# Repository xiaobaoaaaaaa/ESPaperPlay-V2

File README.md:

# ESPaperPlay-V2

基于 **ESP32-S3-WROOM-1-N16R8 + 7.5 英寸电子纸**的多功能平台，逐步实现阅读、音频和网络应用。

这是从 [ESPaperPlay](https://github.com/xiaobaoaaaaaa/ESPaperPlay) 拆分的独立重构仓库。旧版代码的参考起点为 [`0f6d7c3`](https://github.com/xiaobaoaaaaaa/ESPaperPlay/tree/0f6d7c349afdbbeb962a736d84036ce7f8487174)。本库从当前 V2 基线建立新的提交历史，不包含旧固件工程。

## 当前状态

- **当前硬件开发：99 × 99 mm 嘉立创EDA原生工程。** 已完成原生 PCB 布线、标准四层叠层保存和完整 21 项复核，原生 DRC 为 0 连接/0 其他错误，工程审查项仍保留；实际 CAM 及工程审查结论见[原生工程入口](hardware/devboard-99/easyeda-native/README.md)和[同版检查点](hardware/devboard-99/easyeda-native/audit/checkpoint-status.json)。[KiCad r14](hardware/devboard-99/README.md)保留为先期完整布线与电路参考，其独立复核及制造/装配边界见[r14记录](hardware/devboard-99/review-r14/README.md)。尚未制造或实板验证，当前检查不代表制造放行。
- 首批计划做 5 块 PCB，先装 2 块。当前装配资料含元件方向图、手焊接口清单及专用顶层钢网。[99 mm 首板装配资料](hardware/devboard-99/easyeda-native/audit/assembly-review/README.md)
- **固件：M0 骨架。** 应用宿主、活动租约、休眠准备契约、板级配置检查、双槽分区和串口演示已经实现；外设驱动、图形界面和网络应用尚待接入。
- **保留基线：r10 PCB 制造整改完成。** 已移动64个近焊盘过孔，538个普通孔的双面阻焊间距达到≥0.20mm，11个IC热孔指定填平盖帽；官方USB/SD名义阻抗窗口检查通过。原理图r6/r5保持，DRC为0错误、0未连接；已更新独立制板、DIY钢网及203位回流/27位手焊文件，尚未下单或上电。见 [r10记录](docs/v2/hardware/pcb-dfm-r10.md)和[文件包](hardware/devboard-r0/output/manufacturing/r10-review/README.md)。这些制造文件不适用于当前 99 mm 板。
- **历史 r10 首批准备（r11 记录）：** 已按5块PCB、先焊2块及无框钢片整理[工厂审核规格、64种备料表与首板工作单](hardware/devboard-r0/output/manufacturing/r10-first-batch/README.md)。该清单对应旧 r10 PCB，不适用于当前 99 mm 原生工程；当时工厂回复、来料容量和实测未完成。现有 M0 不具备分域维护功能。
- **历史 r10 嘉立创迁移与 CAM：** [旧迁移工程与独立制板/钢网包](hardware/devboard-r0/output/easyeda/r10-cam-checked/README.md)已纳入Git；[最终CAM复核](hardware/devboard-r0/output/easyeda/r10-cam-checked/CAM_REVIEW.md)通过、严格DRC为0。已恢复导入遗漏的阻焊、热焊及铜颈设置；原 KiCad r10 和原制造包仅保留历史对照；该包不能用于当前 99 mm 原生板。
- 未进行新板烧录或上电验证。硬件的充电默认禁用状态、温窗假设及待验证项见硬件文档。

## 目录与入口

| 目录 | 内容 |
| --- | --- |
| [根目录固件工程](docs/v2/firmware.md) | 独立 ESP-IDF 固件、主机测试及板级元数据 |
| [docs/v2/](docs/v2/README.md) | 架构、路线和软硬件设计记录 |
| [hardware/devboard-r0/](hardware/devboard-r0/README.md) | 历史 KiCad r10 基线、嘉立创迁移工程、项目库、检查器和评审记录 |
| [hardware/devboard-99/](hardware/devboard-99/README.md) | 99 mm 开发板：当前嘉立创EDA原生工程及 KiCad r14 对照、原生检查/装配条件 |
| [hardware/reference/](hardware/reference/) | 原厂来源、版本与 SHA-256；原始下载文件仅本地保存 |
| [outputs/](outputs/) | 已审查的 BOM 工作簿 |

设计资料保留 `docs/v2/` 和 `devboard-r0` 路径，使原有工程、检查器及证据链接继续有效；这些目录名不表示当前硬件仍是 r0。

## 验证

主机测试不需要 ESP-IDF：

```sh
cmake -S tests -B build/host -G Ninja \
  -DCMAKE_C_COMPILER=clang -DCMAKE_BUILD_TYPE=Debug
cmake --build build/host
ctest --test-dir build/host --output-on-failure
```

激活 ESP-IDF 6.1 后构建 N16R8 固件：

```sh
idf.py -B build/esp32s3 build
```

固件详细说明见 [固件开发指南](docs/v2/firmware.md)。当前硬件检查命令见 [原生工程说明](hardware/devboard-99/easyeda-native/README.md)和[完整验证入口](hardware/devboard-99/easyeda-native/verification/README-final-runner.md)；公开文件完整性可运行 `python3 tools/verify_repository.py`。原厂 PDF 不随 Git 分发，重新计算依赖 PDF 的温窗模型前，须按相应 `sources.json` 恢复资料。

## 版本管理

`main` 保存已提交的阶段成果，功能开发使用短期分支。硬件设计修订号与 Git 标签分别管理，r5/r6/r7 的历史报告不是对应的历史提交。迁移来源、检查结果和当前基线见 [迁移记录](docs/v2/repository-migration.md)。

当前嘉立创工程入口见[99 mm 原生工程](hardware/devboard-99/easyeda-native/README.md)；旧 r10 迁移历史快照见[历史迁移目录](hardware/devboard-r0/output/easyeda/README.txt)，KiCad r10 仅保留为迁移对照基线。两种工程不会自动双向同步；每次变更须注明所编辑的工程及来源版本，同步更新导出、检查报告与校验清单。历史生成脚本不能覆盖已经手工修改的原理图或PCB。

本项目原创代码与文档沿用 [MIT License](LICENSE)。KiCad 库内容及原厂资料的归属见 [第三方说明](THIRD_PARTY_NOTICES.md)。

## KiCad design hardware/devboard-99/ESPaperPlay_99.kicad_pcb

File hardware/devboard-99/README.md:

# ESPaperPlay 99 mm 开发验证板

当前设计入口为[嘉立创EDA原生工程](easyeda-native/README.md)，以下保留 KiCad r14 的独立参考与复核结果。

**r14：99 × 99 mm、四层、顶面装配；已完成PCB布线与CAD复核。原生DRC 0违规、0未连接、0原理图一致性问题。**

用 KiCad 10 打开本目录的 [ESPaperPlay_99.kicad_pro](ESPaperPlay_99.kicad_pro)，再打开同名PCB，即本次完整走线版。包含独立根原理图、10张子页、本地符号/封装库和规则文件。

保留240个封装、236个电气器件、774个逻辑引脚和181个网络。全部器件仍在顶面，五个按键及全部调试/测流接口、21个操作包络保留。原理图、器件位置、焊盘几何、引脚分配与DNP状态保持r13；原r10和嘉立创迁移工程未修改。

| 项目 | 当前状态 |
|---|---|
| 外形与层叠 | Edge.Cuts中心线99.000×99.000mm；四层名义1.6mm；F/B走线，双内层连续GND |
| 实际布线 | 2591段走线、665个普通过孔；最小线宽/间距0.15mm，普通孔至少0.30/0.60mm |
| 电源与接口 | 24条电源铜路径预算通过；6路SD主路径长度/偏差检查通过；USB两方向差分长度差已量化 |
| 孔与阻焊 | 全部实际孔距与普通过孔双面阻焊距离通过名义几何检查；制造公差仍待厂方验收 |
| 热孔 | U101四个实际普通开窗PTH及圆弧钢网保持；U301十二孔保持；U201/U203/U802八个外移GND孔已实际接通 |
| 充电 | 仍默认禁充：R108 DNP、J105开放；设定电流约0.701A，电池/NTC适配与实测条件保持 |

完整结果、USB回流目标例外、参考面边缘条件及U101印刷/制造验收边界见 [r14复核记录](review-r14/README.md)。[顶面走线](review-r14/front-layout.png)、[装配图](review-r14/assembly-layout.png)、[操作空间](review-r14/access-layout.png)均对应当前PCB。

裸板尺寸满足10×10cm内的目标，表面处理参考OSP；没有要求U101树脂填孔或电镀盖帽，也没有请求或证明±10%阻抗保证。实际叠层、孔环/阻焊和钢网精度、首板焊接/温升/信号完整性仍待验收；CAD通过不代表免费券资格或制造放行。U101局部手工印刷须核验每轴≤±0.030mm对位、钢网边缘≤±0.020mm条件，详见 [r13公差记录](review-r13/README.md)。

已按确认流程在嘉立创EDA使用既有库建立独立原生工程，原生标准四层叠层已保存重开。当前布线、原生 DRC、实际 CAM、工程偏差和首板条件统一见[原生工程检查点](easyeda-native/README.md)；本页前述 r14 数字是 KiCad 对照结果，不等同于原生工程检查结论。尚未制造放行，未上传工厂或下单；旧 r10 制板和钢网包不能用于本 99 mm 版。

历史依据：[r12布局/机械基线](review-r12/layout-review.md)、[r13热孔与钢网](review-r13/README.md)。复现检查见 [工具说明](tools/README.md)。

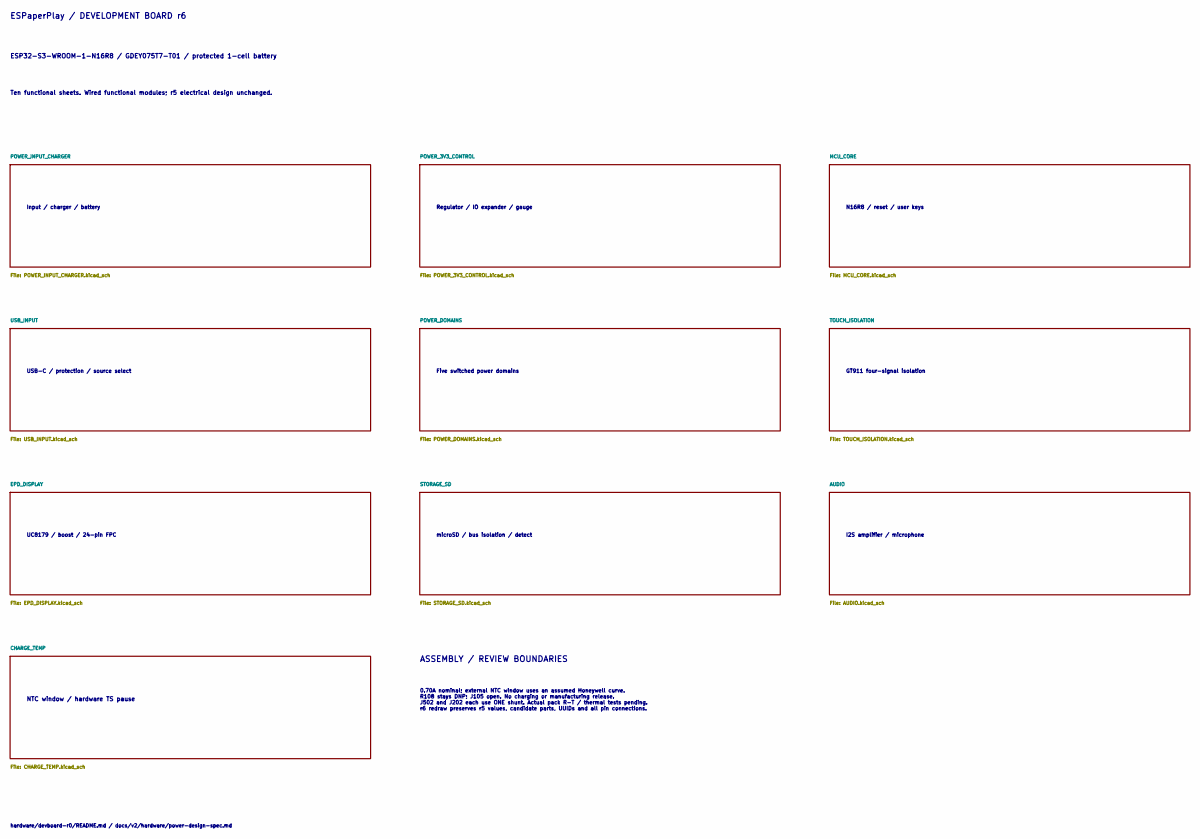
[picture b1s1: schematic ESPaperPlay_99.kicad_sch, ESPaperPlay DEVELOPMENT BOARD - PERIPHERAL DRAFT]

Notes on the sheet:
ESPaperPlay / DEVELOPMENT BOARD r6
ESP32-S3-WROOM-1-N16R8 / GDEY075T7-T01 / protected 1-cell battery
Ten functional sheets. Wired functional modules; r5 electrical design unchanged.
Input / charger / battery
Regulator / IO expander / gauge
N16R8 / reset / user keys
USB-C / protection / source select
Five switched power domains
GT911 four-signal isolation
UC8179 / boost / 24-pin FPC
microSD / bus isolation / detect
I2S amplifier / microphone
ASSEMBLY / REVIEW BOUNDARIES
0.70A nominal; external NTC window uses an assumed Honeywell curve. R108 stays DNP; J105 open. No charging or manufacturing release. J502 and J202 each use ONE shunt. Actual pack R-T / thermal tests pending. r6 redraw preserves r5 values, candidate parts, UUIDs and all pin connections.
hardware/devboard-r0/README.md / docs/v2/hardware/power-design-spec.md
NTC window / hardware TS pause

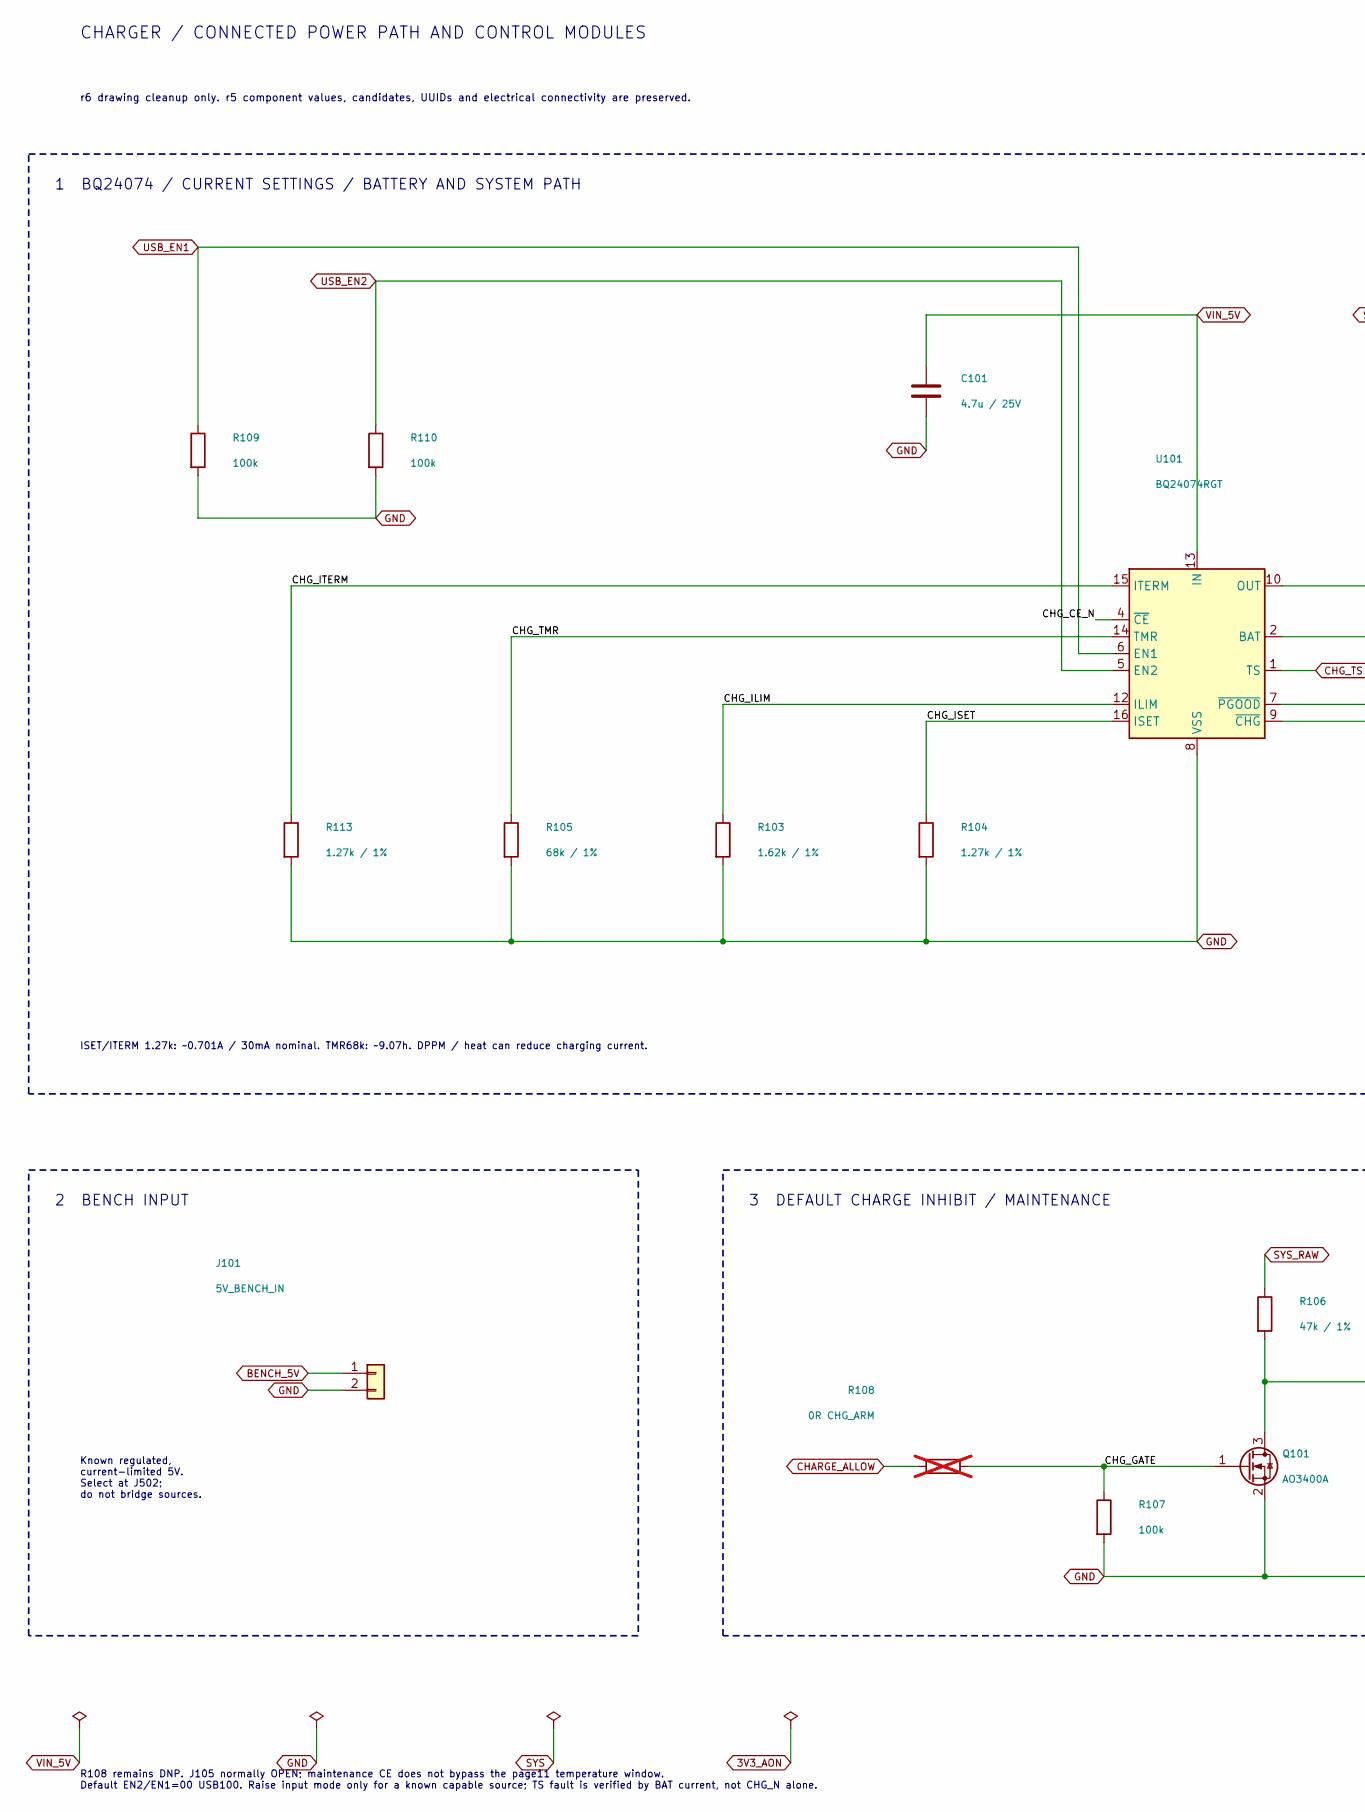
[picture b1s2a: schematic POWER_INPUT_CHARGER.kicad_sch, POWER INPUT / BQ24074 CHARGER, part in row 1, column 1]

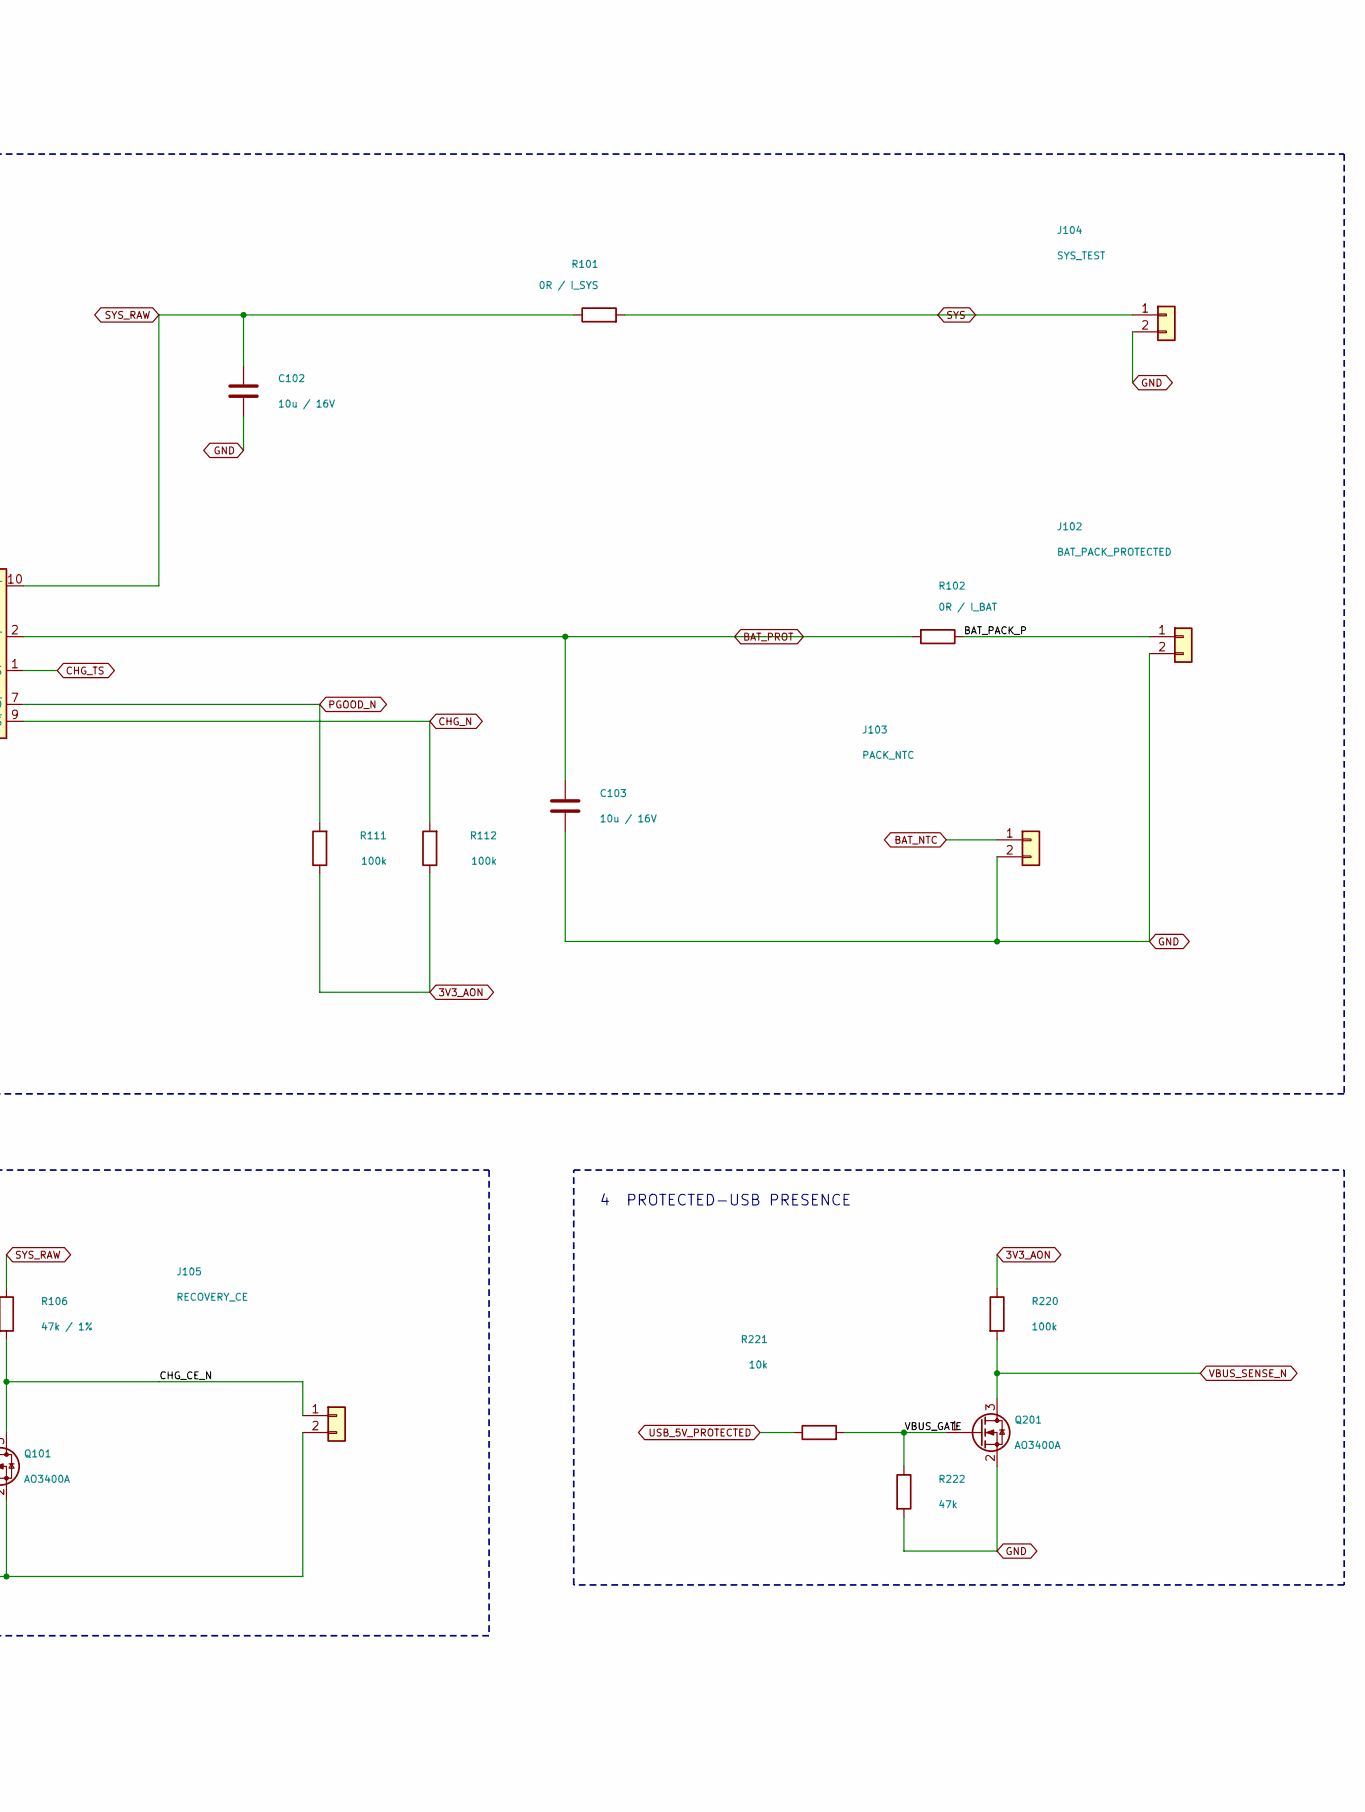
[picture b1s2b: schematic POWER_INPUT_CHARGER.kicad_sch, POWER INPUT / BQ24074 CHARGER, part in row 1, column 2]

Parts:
C101: 4.7u / 25V; C_0805_2012Metric
C102, C103: 10u / 16V; C_1206_3216Metric
J101: 5V_BENCH_IN; WR_PHD_1x02_P2.54_Drill1.10
J102: BAT_PACK_PROTECTED; PhoenixContact_MKDS-1-2-3.5_1751248_1x02_P3.50mm_Horizontal
J103: PACK_NTC; PhoenixContact_MKDS-1-2-3.5_1751248_1x02_P3.50mm_Horizontal
J104: SYS_TEST; WR_PHD_1x02_P2.54_Drill1.10
J105: RECOVERY_CE; WR_PHD_1x02_P2.54_Drill1.10
Q101, Q201: AO3400A; AOS_SOT23_PO00001N
R101: 0R / I_SYS; Bourns_CRF0805_Jumper
R102: 0R / I_BAT; Bourns_CRF0805_Jumper
R103: 1.62k / 1%; R_0603_1608Metric
R104, R113: 1.27k / 1%; R_0603_1608Metric
R105: 68k / 1%; R_0603_1608Metric
R106: 47k / 1%; R_0603_1608Metric
R107, R109, R110, R111, R112, R220: 100k; R_0603_1608Metric
R108: 0R CHG_ARM; R_0603_1608Metric; not fitted
R221: 10k; R_0603_1608Metric
R222: 47k; R_0603_1608Metric
U101: BQ24074RGT; TI_RGT0016C_VQFN_3x3mm_P0.5mm_EP1.68mm

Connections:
3V3_AON: R111.1, R112.1, R220.1; also elsewhere on the board
/POWER_INPUT_CHARGER/BAT_PACK_P: J102.1, R102.1
/POWER_INPUT_CHARGER/CHG_CE_N: J105.1, Q101.3 (D), R106.2, U101.4 (~CE)
/POWER_INPUT_CHARGER/CHG_GATE: Q101.1 (G), R107.1, R108.2
/POWER_INPUT_CHARGER/CHG_ILIM: R103.1, U101.12 (ILIM)
/POWER_INPUT_CHARGER/CHG_ISET: R104.1, U101.16 (ISET)
/POWER_INPUT_CHARGER/CHG_ITERM: R113.1, U101.15 (ITERM)
/POWER_INPUT_CHARGER/CHG_TMR: R105.1, U101.14 (TMR)
/POWER_INPUT_CHARGER/VBUS_GATE: Q201.1 (G), R221.2, R222.1
BAT_NTC: J103.1; also elsewhere on the board
BAT_PROT: C103.1, R102.2, U101.2 (BAT), U101.3 (BAT); also elsewhere on the board
BENCH_5V: J101.1; also elsewhere on the board
CHARGE_ALLOW: R108.1; also elsewhere on the board
CHG_N: R112.2, U101.9 (~CHG); also elsewhere on the board
CHG_TS: U101.1 (TS); also elsewhere on the board
GND: C101.2, C102.2, C103.2, J101.2, J102.2, J103.2, J104.2, J105.2, Q101.2 (S), Q201.2 (S), R103.2, R104.2, R105.2, R107.2, R109.2, R110.2, R113.2, R222.2, U101.8 (VSS), U101.17 (VSS); also elsewhere on the board
PGOOD_N: R111.2, U101.7 (~PGOOD); also elsewhere on the board
SYS: J104.1, R101.2; also elsewhere on the board
SYS_RAW: C102.1, R101.1, R106.1, U101.10 (OUT), U101.11 (OUT)
USB_5V_PROTECTED: R221.1; also elsewhere on the board
USB_EN1: R109.1, U101.6 (EN1); also elsewhere on the board
USB_EN2: R110.1, U101.5 (EN2); also elsewhere on the board
VBUS_SENSE_N: Q201.3 (D), R220.2; also elsewhere on the board
VIN_5V: C101.1, U101.13 (IN); also elsewhere on the board

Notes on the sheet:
CHARGER / CONNECTED POWER PATH AND CONTROL MODULES
r6 drawing cleanup only. r5 component values, candidates, UUIDs and electrical connectivity are preserved.
1 BQ24074 / CURRENT SETTINGS / BATTERY AND SYSTEM PATH
ISET/ITERM 1.27k: ~0.701A / 30mA nominal. TMR68k: ~9.07h. DPPM / heat can reduce charging current.
2 BENCH INPUT
Known regulated, current-limited 5V. Select at J502; do not bridge sources.
3 DEFAULT CHARGE INHIBIT / MAINTENANCE
4 PROTECTED-USB PRESENCE
R108 remains DNP. J105 normally OPEN; maintenance CE does not bypass the page11 temperature window. Default EN2/EN1=00 USB100. Raise input mode only for a known capable source; TS fault is verified by BAT current, not CHG_N alone.

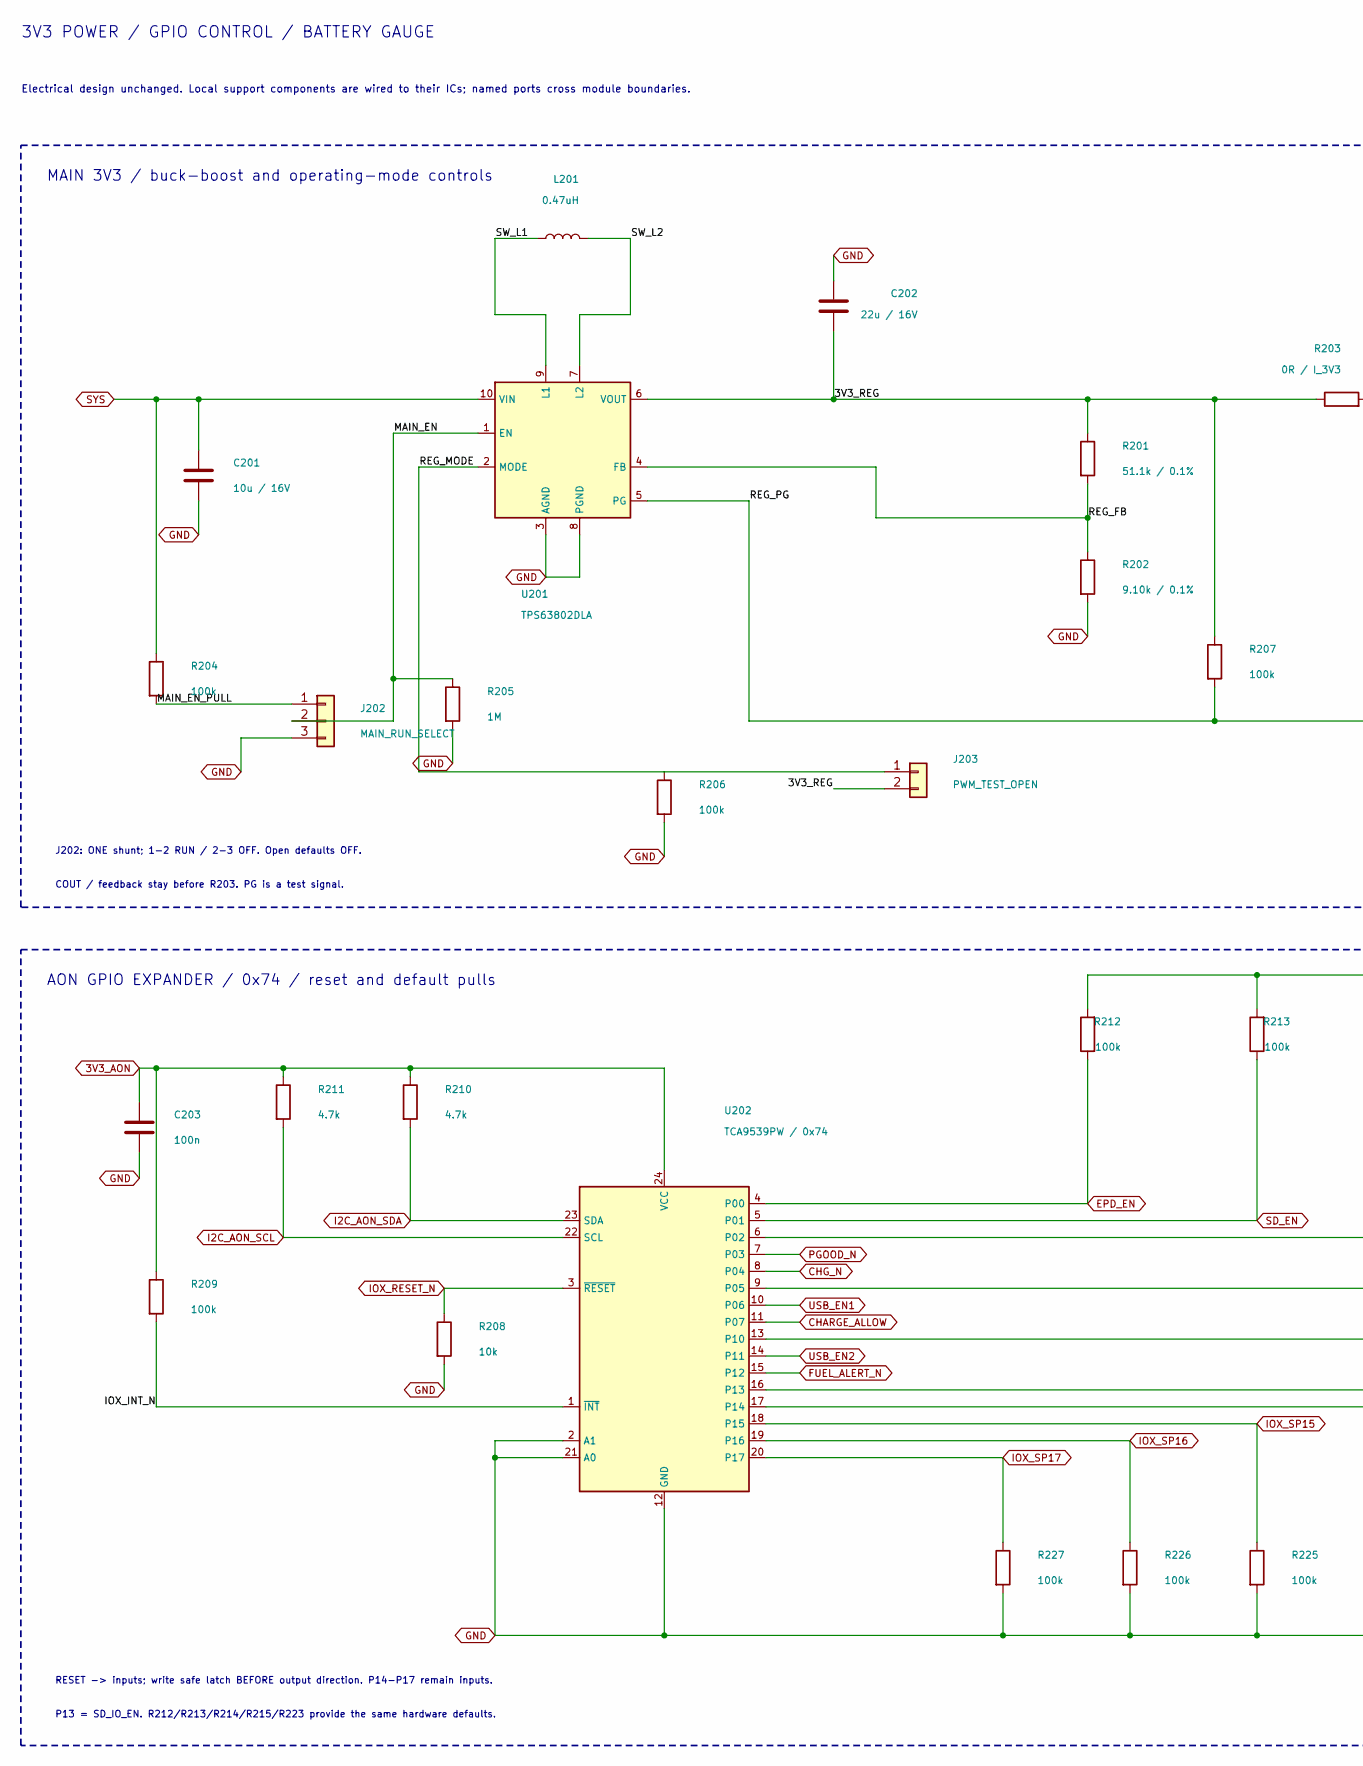
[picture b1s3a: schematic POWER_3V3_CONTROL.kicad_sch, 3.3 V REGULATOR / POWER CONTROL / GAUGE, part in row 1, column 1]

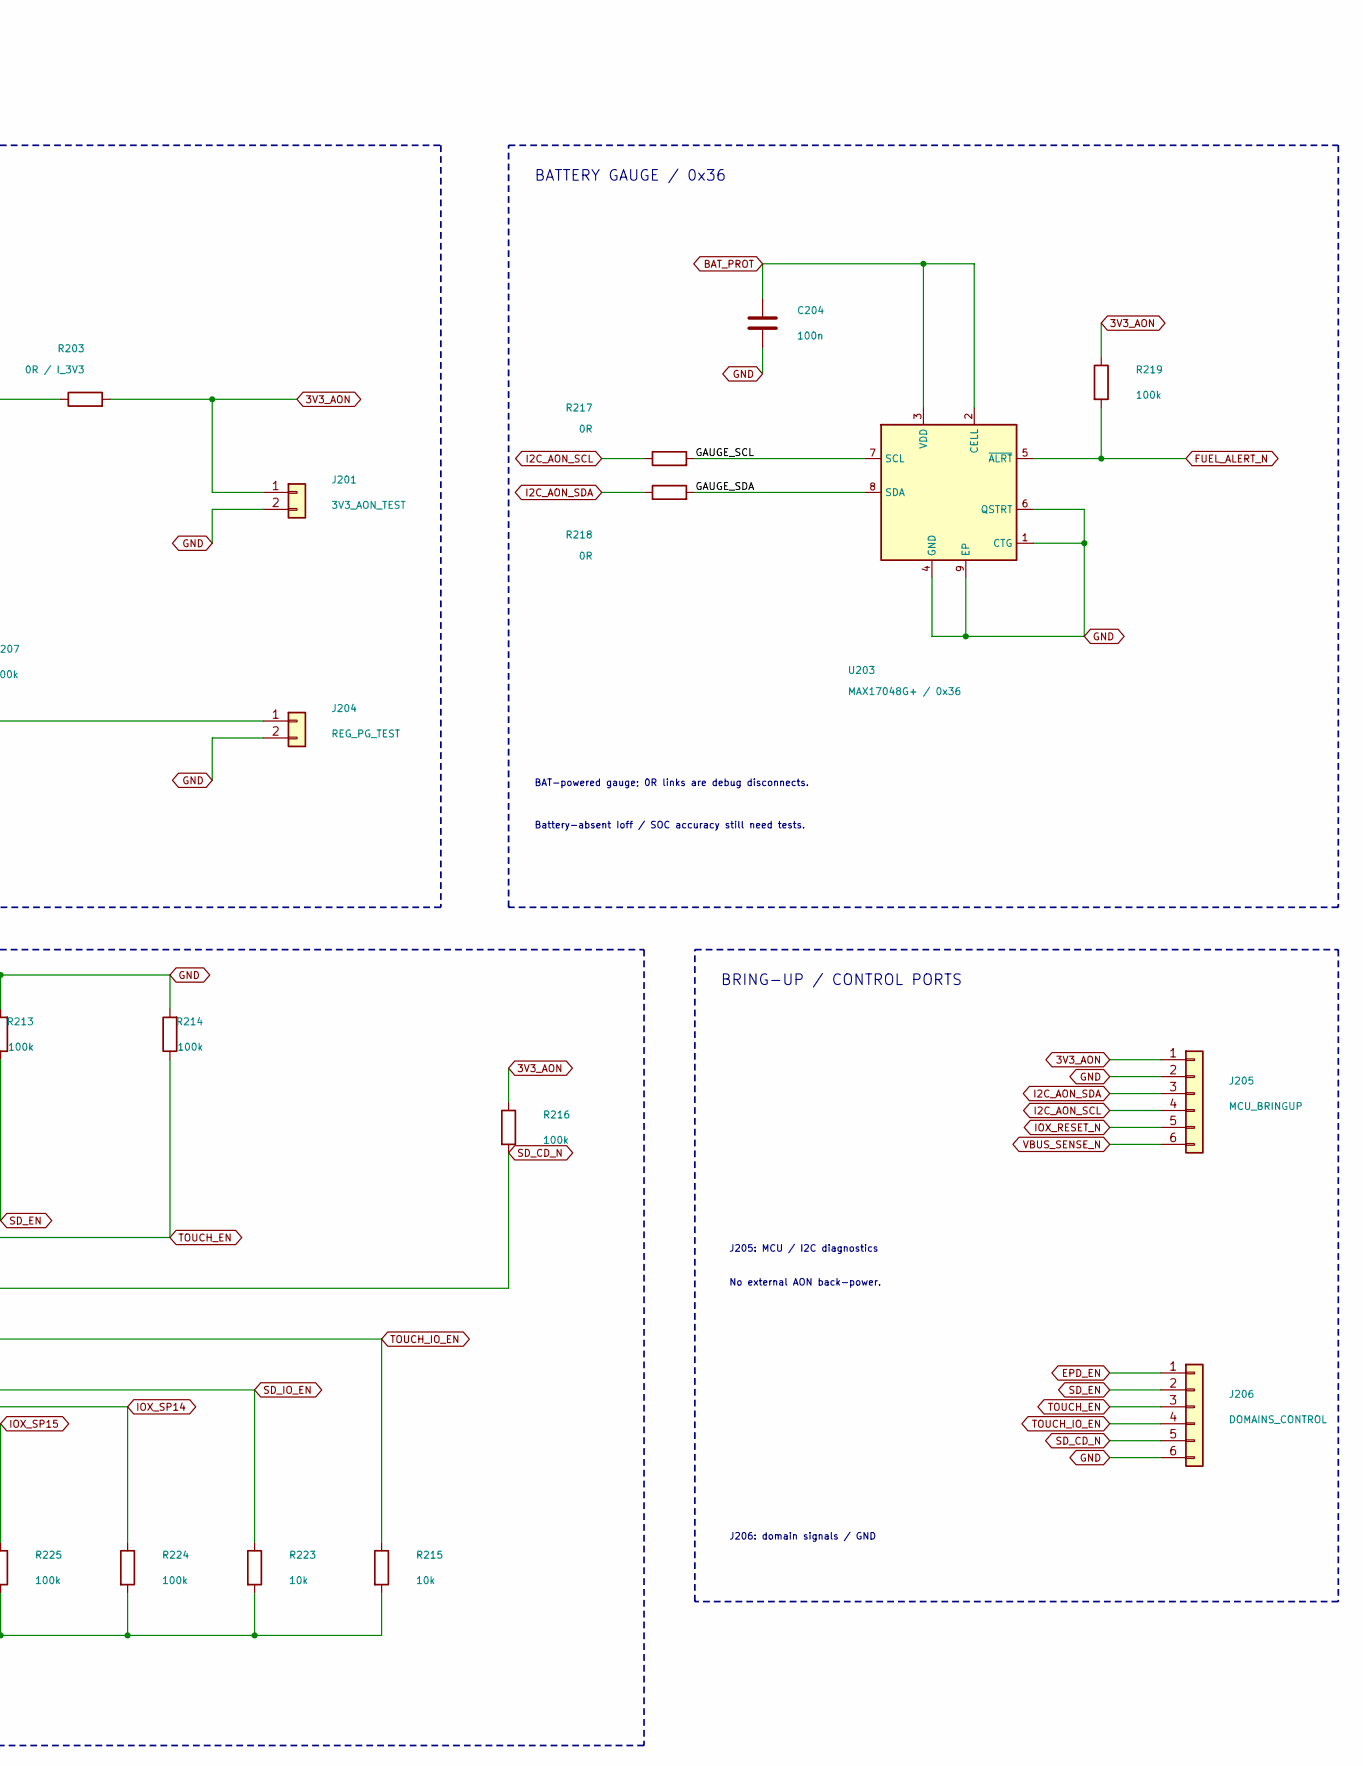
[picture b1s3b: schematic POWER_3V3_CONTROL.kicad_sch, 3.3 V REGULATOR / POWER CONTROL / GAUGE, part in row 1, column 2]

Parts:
C201: 10u / 16V; C_1206_3216Metric
C202: 22u / 16V; C_1206_3216Metric
C203, C204: 100n; C_0603_1608Metric
J201: 3V3_AON_TEST; WR_PHD_1x02_P2.54_Drill1.10
J202: MAIN_RUN_SELECT; WR_PHD_1x03_P2.54_Drill1.10
J203: PWM_TEST_OPEN; WR_PHD_1x02_P2.54_Drill1.10
J204: REG_PG_TEST; WR_PHD_1x02_P2.54_Drill1.10
J205: MCU_BRINGUP; WR_PHD_1x06_P2.54_Drill1.10
J206: DOMAINS_CONTROL; WR_PHD_1x06_P2.54_Drill1.10
L201: 0.47uH; Coilcraft_XFL4015_4x4mm
R201: 51.1k / 0.1%; R_0603_1608Metric
R202: 9.10k / 0.1%; R_0603_1608Metric
R203: 0R / I_3V3; Bourns_CRF0805_Jumper
R204, R206, R207, R209, R212, R213, R214, R216, R219, R224, R225, R226, R227: 100k; R_0603_1608Metric
R205: 1M; R_0603_1608Metric
R208, R215, R223: 10k; R_0603_1608Metric
R210, R211: 4.7k; R_0603_1608Metric
R217, R218: 0R; R_0603_1608Metric
U201: TPS63802DLA; TI_DLA0010A_VSON-HR_2x3mm_P0.5mm
U202: TCA9539PW / 0x74; TSSOP-24_4.4x7.8mm_P0.65mm
U203: MAX17048G+ / 0x36; TDFN-8-1EP_2x2mm_P0.5mm_EP0.8x1.2mm

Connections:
3V3_AON: C203.1, J201.1, J205.1, R203.2, R209.1, R210.1, R211.1, R216.1, R219.1, U202.24 (VCC); also elsewhere on the board
/POWER_3V3_CONTROL/3V3_REG: C202.1, J203.2, R201.1, R203.1, R207.1, U201.6 (VOUT)
/POWER_3V3_CONTROL/GAUGE_SCL: R217.2, U203.7 (SCL)
/POWER_3V3_CONTROL/GAUGE_SDA: R218.2, U203.8 (SDA)
/POWER_3V3_CONTROL/IOX_INT_N: R209.2, U202.1 (~INT)
/POWER_3V3_CONTROL/MAIN_EN: J202.2, R205.1, U201.1 (EN)
/POWER_3V3_CONTROL/MAIN_EN_PULL: J202.1, R204.2
/POWER_3V3_CONTROL/REG_FB: R201.2, R202.1, U201.4 (FB)
/POWER_3V3_CONTROL/REG_MODE: J203.1, R206.1, U201.2 (MODE)
/POWER_3V3_CONTROL/REG_PG: J204.1, R207.2, U201.5 (PG)
/POWER_3V3_CONTROL/SW_L1: L201.1, U201.9 (L1)
/POWER_3V3_CONTROL/SW_L2: L201.2, U201.7 (L2)
BAT_PROT: C204.1, U203.2 (CELL), U203.3 (VDD); also elsewhere on the board
CHARGE_ALLOW: U202.11 (P07); also elsewhere on the board
CHG_N: U202.8 (P04); also elsewhere on the board
EPD_EN: J206.1, R212.1, U202.4 (P00); also elsewhere on the board
FUEL_ALERT_N: R219.2, U202.15 (P12), U203.5 (~ALRT)
GND: C201.2, C202.2, C203.2, C204.2, J201.2, J202.3, J204.2, J205.2, J206.6, R202.2, R205.2, R206.2, R208.2, R212.2, R213.2, R214.2, R215.2, R223.2, R224.2, R225.2, R226.2, R227.2, U201.3 (AGND), U201.8 (PGND), U202.2 (A1), U202.12 (GND), U202.21 (A0), U203.1 (CTG), U203.4 (GND), U203.6 (QSTRT), U203.9 (EP); also elsewhere on the board
I2C_AON_SCL: J205.4, R211.2, R217.1, U202.22 (SCL); also elsewhere on the board
I2C_AON_SDA: J205.3, R210.2, R218.1, U202.23 (SDA); also elsewhere on the board
IOX_RESET_N: J205.5, R208.1, U202.3 (~RESET); also elsewhere on the board
IOX_SP14: R224.1, U202.17 (P14)
IOX_SP15: R225.1, U202.18 (P15)
IOX_SP16: R226.1, U202.19 (P16)
IOX_SP17: R227.1, U202.20 (P17)
PGOOD_N: U202.7 (P03); also elsewhere on the board
SD_CD_N: J206.5, R216.2, U202.9 (P05); also elsewhere on the board
SD_EN: J206.2, R213.1, U202.5 (P01); also elsewhere on the board
SD_IO_EN: R223.1, U202.16 (P13); also elsewhere on the board
SYS: C201.1, R204.1, U201.10 (VIN); also elsewhere on the board
TOUCH_EN: J206.3, R214.1, U202.6 (P02); also elsewhere on the board
TOUCH_IO_EN: J206.4, R215.1, U202.13 (P10); also elsewhere on the board
USB_EN1: U202.10 (P06); also elsewhere on the board
USB_EN2: U202.14 (P11); also elsewhere on the board
VBUS_SENSE_N: J205.6; also elsewhere on the board

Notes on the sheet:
3V3 POWER / GPIO CONTROL / BATTERY GAUGE
Electrical design unchanged. Local support components are wired to their ICs; named ports cross module boundaries.
MAIN 3V3 / buck-boost and operating-mode controls
BATTERY GAUGE / 0x36
AON GPIO EXPANDER / 0x74 / reset and default pulls
BRING-UP / CONTROL PORTS
J202: ONE shunt; 1-2 RUN / 2-3 OFF. Open defaults OFF.
COUT / feedback stay before R203. PG is a test signal.
BAT-powered gauge; 0R links are debug disconnects.
Battery-absent Ioff / SOC accuracy still need tests.
RESET -> inputs; write safe latch BEFORE output direction. P14-P17 remain inputs.
P13 = SD_IO_EN. R212/R213/R214/R215/R223 provide the same hardware defaults.
J205: MCU / I2C diagnostics
No external AON back-power.
J206: domain signals / GND
